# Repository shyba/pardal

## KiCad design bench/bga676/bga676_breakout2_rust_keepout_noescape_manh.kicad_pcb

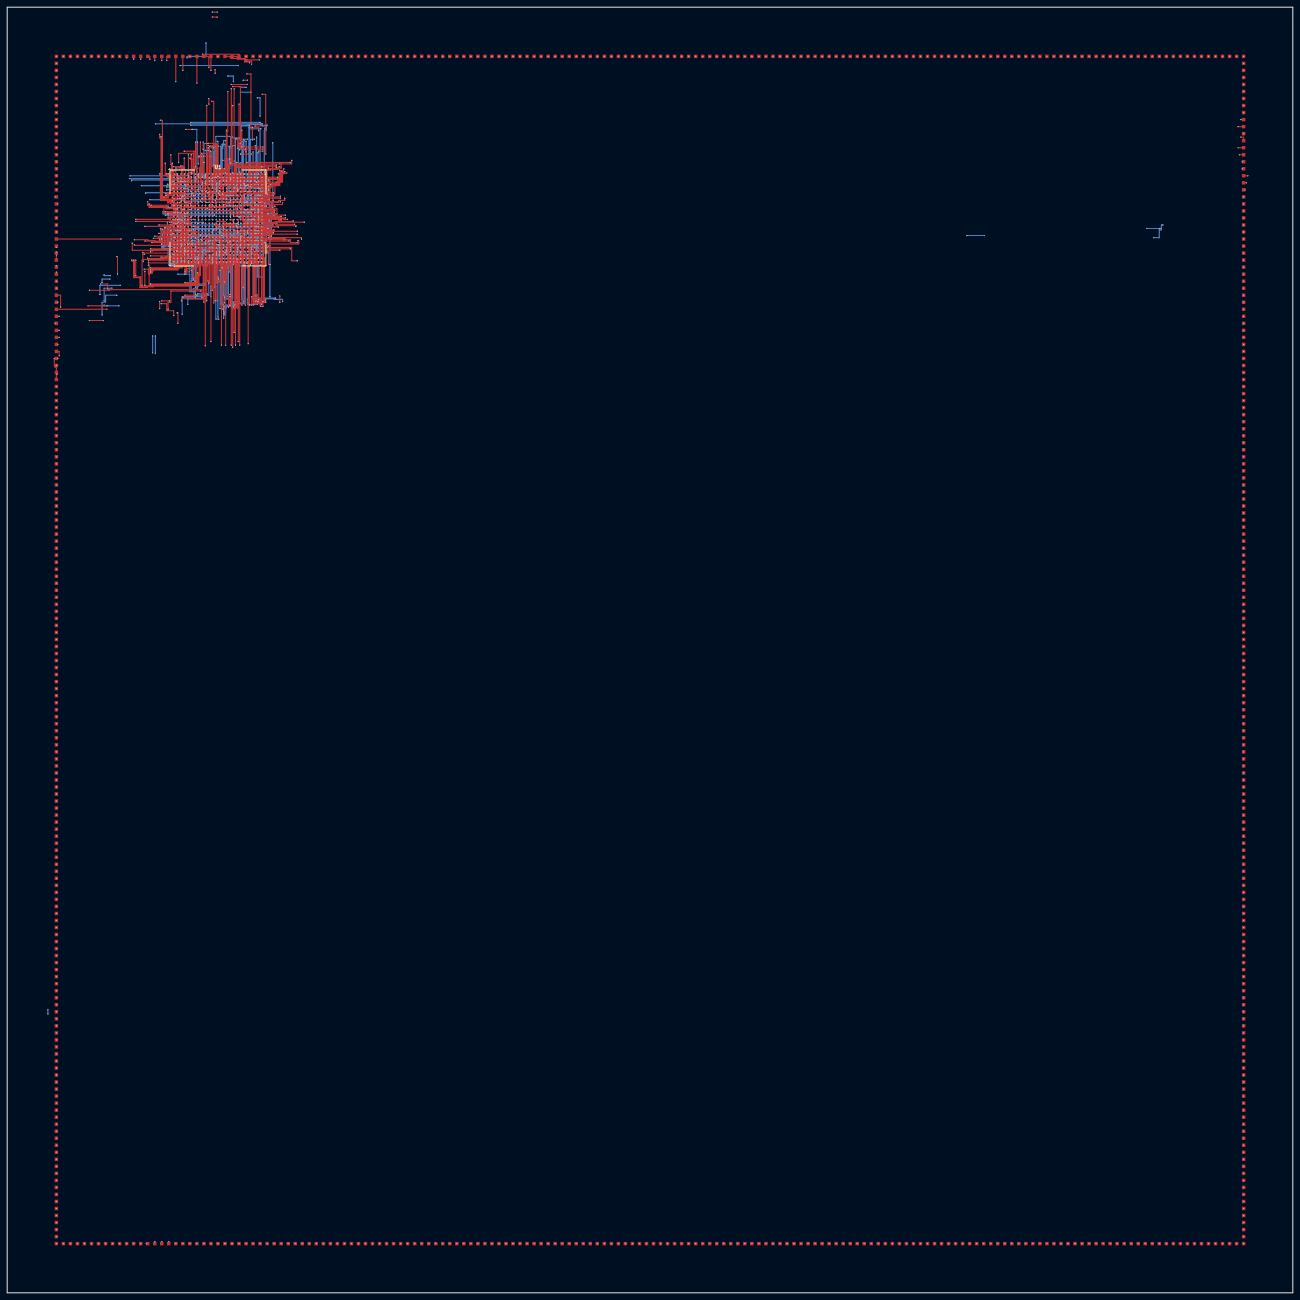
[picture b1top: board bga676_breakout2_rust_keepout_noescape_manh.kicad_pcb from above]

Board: 4 copper layers, 366.0 x 366.0 mm, 677 parts (0 on the bottom side), 676 nets.

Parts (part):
TP1: A1; TestPoint_Pad_1.0x1.0mm
TP2: A2; TestPoint_Pad_1.0x1.0mm
TP3: A3; TestPoint_Pad_1.0x1.0mm
TP4: A4; TestPoint_Pad_1.0x1.0mm
TP5: A5; TestPoint_Pad_1.0x1.0mm
TP6: A6; TestPoint_Pad_1.0x1.0mm
TP7: A7; TestPoint_Pad_1.0x1.0mm
TP8: A8; TestPoint_Pad_1.0x1.0mm
TP9: A9; TestPoint_Pad_1.0x1.0mm
TP10: A10; TestPoint_Pad_1.0x1.0mm
TP11: A11; TestPoint_Pad_1.0x1.0mm
TP12: A12; TestPoint_Pad_1.0x1.0mm
TP13: A13; TestPoint_Pad_1.0x1.0mm
TP14: A14; TestPoint_Pad_1.0x1.0mm
TP15: A15; TestPoint_Pad_1.0x1.0mm
TP16: A16; TestPoint_Pad_1.0x1.0mm
TP17: A17; TestPoint_Pad_1.0x1.0mm
TP18: A18; TestPoint_Pad_1.0x1.0mm
TP19: A19; TestPoint_Pad_1.0x1.0mm
TP20: A20; TestPoint_Pad_1.0x1.0mm
TP21: A21; TestPoint_Pad_1.0x1.0mm
TP22: A22; TestPoint_Pad_1.0x1.0mm
TP23: A23; TestPoint_Pad_1.0x1.0mm
TP24: A24; TestPoint_Pad_1.0x1.0mm
TP25: A25; TestPoint_Pad_1.0x1.0mm
TP26: A26; TestPoint_Pad_1.0x1.0mm
TP27: B1; TestPoint_Pad_1.0x1.0mm
TP28: B2; TestPoint_Pad_1.0x1.0mm
TP29: B3; TestPoint_Pad_1.0x1.0mm
TP30: B4; TestPoint_Pad_1.0x1.0mm
TP31: B5; TestPoint_Pad_1.0x1.0mm
TP32: B6; TestPoint_Pad_1.0x1.0mm
TP33: B7; TestPoint_Pad_1.0x1.0mm
TP34: B8; TestPoint_Pad_1.0x1.0mm
TP35: B9; TestPoint_Pad_1.0x1.0mm
TP36: B10; TestPoint_Pad_1.0x1.0mm
TP37: B11; TestPoint_Pad_1.0x1.0mm
TP38: B12; TestPoint_Pad_1.0x1.0mm
TP39: B13; TestPoint_Pad_1.0x1.0mm
TP40: B14; TestPoint_Pad_1.0x1.0mm
TP41: B15; TestPoint_Pad_1.0x1.0mm
TP42: B16; TestPoint_Pad_1.0x1.0mm
TP43: B17; TestPoint_Pad_1.0x1.0mm
TP44: B18; TestPoint_Pad_1.0x1.0mm
TP45: B19; TestPoint_Pad_1.0x1.0mm
TP46: B20; TestPoint_Pad_1.0x1.0mm
TP47: B21; TestPoint_Pad_1.0x1.0mm
TP48: B22; TestPoint_Pad_1.0x1.0mm
TP49: B23; TestPoint_Pad_1.0x1.0mm
TP50: B24; TestPoint_Pad_1.0x1.0mm
TP51: B25; TestPoint_Pad_1.0x1.0mm
TP52: B26; TestPoint_Pad_1.0x1.0mm
TP53: C1; TestPoint_Pad_1.0x1.0mm
TP54: C2; TestPoint_Pad_1.0x1.0mm
TP55: C3; TestPoint_Pad_1.0x1.0mm
TP56: C4; TestPoint_Pad_1.0x1.0mm
TP57: C5; TestPoint_Pad_1.0x1.0mm
TP58: C6; TestPoint_Pad_1.0x1.0mm
TP59: C7; TestPoint_Pad_1.0x1.0mm
TP60: C8; TestPoint_Pad_1.0x1.0mm
TP61: C9; TestPoint_Pad_1.0x1.0mm
TP62: C10; TestPoint_Pad_1.0x1.0mm
TP63: C11; TestPoint_Pad_1.0x1.0mm
TP64: C12; TestPoint_Pad_1.0x1.0mm
TP65: C13; TestPoint_Pad_1.0x1.0mm
TP66: C14; TestPoint_Pad_1.0x1.0mm
TP67: C15; TestPoint_Pad_1.0x1.0mm
TP68: C16; TestPoint_Pad_1.0x1.0mm
TP69: C17; TestPoint_Pad_1.0x1.0mm
TP70: C18; TestPoint_Pad_1.0x1.0mm
TP71: C19; TestPoint_Pad_1.0x1.0mm
TP72: C20; TestPoint_Pad_1.0x1.0mm
TP73: C21; TestPoint_Pad_1.0x1.0mm
TP74: C22; TestPoint_Pad_1.0x1.0mm
TP75: C23; TestPoint_Pad_1.0x1.0mm
TP76: C24; TestPoint_Pad_1.0x1.0mm
TP77: C25; TestPoint_Pad_1.0x1.0mm
TP78: C26; TestPoint_Pad_1.0x1.0mm
TP79: D1; TestPoint_Pad_1.0x1.0mm
TP80: D2; TestPoint_Pad_1.0x1.0mm
TP81: D3; TestPoint_Pad_1.0x1.0mm
TP82: D4; TestPoint_Pad_1.0x1.0mm
TP83: D5; TestPoint_Pad_1.0x1.0mm
TP84: D6; TestPoint_Pad_1.0x1.0mm
TP85: D7; TestPoint_Pad_1.0x1.0mm
TP86: D8; TestPoint_Pad_1.0x1.0mm
TP87: D9; TestPoint_Pad_1.0x1.0mm
TP88: D10; TestPoint_Pad_1.0x1.0mm
TP89: D11; TestPoint_Pad_1.0x1.0mm
TP90: D12; TestPoint_Pad_1.0x1.0mm
TP91: D13; TestPoint_Pad_1.0x1.0mm
TP92: D14; TestPoint_Pad_1.0x1.0mm
TP93: D15; TestPoint_Pad_1.0x1.0mm
TP94: D16; TestPoint_Pad_1.0x1.0mm
TP95: D17; TestPoint_Pad_1.0x1.0mm
TP96: D18; TestPoint_Pad_1.0x1.0mm
TP97: D19; TestPoint_Pad_1.0x1.0mm
TP98: D20; TestPoint_Pad_1.0x1.0mm
TP99: D21; TestPoint_Pad_1.0x1.0mm
TP100: D22; TestPoint_Pad_1.0x1.0mm
TP101: D23; TestPoint_Pad_1.0x1.0mm
TP102: D24; TestPoint_Pad_1.0x1.0mm
TP103: D25; TestPoint_Pad_1.0x1.0mm
TP104: D26; TestPoint_Pad_1.0x1.0mm
TP105: E1; TestPoint_Pad_1.0x1.0mm
TP106: E2; TestPoint_Pad_1.0x1.0mm
TP107: E3; TestPoint_Pad_1.0x1.0mm
TP108: E4; TestPoint_Pad_1.0x1.0mm
TP109: E5; TestPoint_Pad_1.0x1.0mm
TP110: E6; TestPoint_Pad_1.0x1.0mm
TP111: E7; TestPoint_Pad_1.0x1.0mm
TP112: E8; TestPoint_Pad_1.0x1.0mm
TP113: E9; TestPoint_Pad_1.0x1.0mm
TP114: E10; TestPoint_Pad_1.0x1.0mm
TP115: E11; TestPoint_Pad_1.0x1.0mm
TP116: E12; TestPoint_Pad_1.0x1.0mm
TP117: E13; TestPoint_Pad_1.0x1.0mm
TP118: E14; TestPoint_Pad_1.0x1.0mm
TP119: E15; TestPoint_Pad_1.0x1.0mm
TP120: E16; TestPoint_Pad_1.0x1.0mm
TP121: E17; TestPoint_Pad_1.0x1.0mm
TP122: E18; TestPoint_Pad_1.0x1.0mm
TP123: E19; TestPoint_Pad_1.0x1.0mm
TP124: E20; TestPoint_Pad_1.0x1.0mm
TP125: E21; TestPoint_Pad_1.0x1.0mm
TP126: E22; TestPoint_Pad_1.0x1.0mm
TP127: E23; TestPoint_Pad_1.0x1.0mm
TP128: E24; TestPoint_Pad_1.0x1.0mm
TP129: E25; TestPoint_Pad_1.0x1.0mm
TP130: E26; TestPoint_Pad_1.0x1.0mm
TP131: F1; TestPoint_Pad_1.0x1.0mm
TP132: F2; TestPoint_Pad_1.0x1.0mm
TP133: F3; TestPoint_Pad_1.0x1.0mm
TP134: F4; TestPoint_Pad_1.0x1.0mm
TP135: F5; TestPoint_Pad_1.0x1.0mm
TP136: F6; TestPoint_Pad_1.0x1.0mm
TP137: F7; TestPoint_Pad_1.0x1.0mm
TP138: F8; TestPoint_Pad_1.0x1.0mm
TP139: F9; TestPoint_Pad_1.0x1.0mm
TP140: F10; TestPoint_Pad_1.0x1.0mm
TP141: F11; TestPoint_Pad_1.0x1.0mm
TP142: F12; TestPoint_Pad_1.0x1.0mm
TP143: F13; TestPoint_Pad_1.0x1.0mm
TP144: F14; TestPoint_Pad_1.0x1.0mm
TP145: F15; TestPoint_Pad_1.0x1.0mm
TP146: F16; TestPoint_Pad_1.0x1.0mm
TP147: F17; TestPoint_Pad_1.0x1.0mm
TP148: F18; TestPoint_Pad_1.0x1.0mm
TP149: F19; TestPoint_Pad_1.0x1.0mm
TP150: F20; TestPoint_Pad_1.0x1.0mm
TP151: F21; TestPoint_Pad_1.0x1.0mm
TP152: F22; TestPoint_Pad_1.0x1.0mm
TP153: F23; TestPoint_Pad_1.0x1.0mm
TP154: F24; TestPoint_Pad_1.0x1.0mm
TP155: F25; TestPoint_Pad_1.0x1.0mm
TP156: F26; TestPoint_Pad_1.0x1.0mm
TP157: G1; TestPoint_Pad_1.0x1.0mm
TP158: G2; TestPoint_Pad_1.0x1.0mm
TP159: G3; TestPoint_Pad_1.0x1.0mm
TP160: G4; TestPoint_Pad_1.0x1.0mm
TP161: G5; TestPoint_Pad_1.0x1.0mm
TP162: G6; TestPoint_Pad_1.0x1.0mm
TP163: G7; TestPoint_Pad_1.0x1.0mm
TP164: G8; TestPoint_Pad_1.0x1.0mm
TP165: G9; TestPoint_Pad_1.0x1.0mm
TP166: G10; TestPoint_Pad_1.0x1.0mm
TP167: G11; TestPoint_Pad_1.0x1.0mm
TP168: G12; TestPoint_Pad_1.0x1.0mm
TP169: G13; TestPoint_Pad_1.0x1.0mm
TP170: G14; TestPoint_Pad_1.0x1.0mm
TP171: G15; TestPoint_Pad_1.0x1.0mm
TP172: G16; TestPoint_Pad_1.0x1.0mm
TP173: G17; TestPoint_Pad_1.0x1.0mm
TP174: G18; TestPoint_Pad_1.0x1.0mm
TP175: G19; TestPoint_Pad_1.0x1.0mm
TP176: G20; TestPoint_Pad_1.0x1.0mm
TP177: G21; TestPoint_Pad_1.0x1.0mm
TP178: G22; TestPoint_Pad_1.0x1.0mm
TP179: G23; TestPoint_Pad_1.0x1.0mm
TP180: G24; TestPoint_Pad_1.0x1.0mm
TP181: G25; TestPoint_Pad_1.0x1.0mm
TP182: G26; TestPoint_Pad_1.0x1.0mm
TP183: H1; TestPoint_Pad_1.0x1.0mm
TP184: H2; TestPoint_Pad_1.0x1.0mm
TP185: H3; TestPoint_Pad_1.0x1.0mm
TP186: H4; TestPoint_Pad_1.0x1.0mm
TP187: H5; TestPoint_Pad_1.0x1.0mm
TP188: H6; TestPoint_Pad_1.0x1.0mm
TP189: H7; TestPoint_Pad_1.0x1.0mm
TP190: H8; TestPoint_Pad_1.0x1.0mm
TP191: H9; TestPoint_Pad_1.0x1.0mm
TP192: H10; TestPoint_Pad_1.0x1.0mm
TP193: H11; TestPoint_Pad_1.0x1.0mm
TP194: H12; TestPoint_Pad_1.0x1.0mm
TP195: H13; TestPoint_Pad_1.0x1.0mm
TP196: H14; TestPoint_Pad_1.0x1.0mm
TP197: H15; TestPoint_Pad_1.0x1.0mm
TP198: H16; TestPoint_Pad_1.0x1.0mm
TP199: H17; TestPoint_Pad_1.0x1.0mm
TP200: H18; TestPoint_Pad_1.0x1.0mm
TP201: H19; TestPoint_Pad_1.0x1.0mm
TP202: H20; TestPoint_Pad_1.0x1.0mm
TP203: H21; TestPoint_Pad_1.0x1.0mm
TP204: H22; TestPoint_Pad_1.0x1.0mm
TP205: H23; TestPoint_Pad_1.0x1.0mm
TP206: H24; TestPoint_Pad_1.0x1.0mm
TP207: H25; TestPoint_Pad_1.0x1.0mm
TP208: H26; TestPoint_Pad_1.0x1.0mm
TP209: J1; TestPoint_Pad_1.0x1.0mm
TP210: J2; TestPoint_Pad_1.0x1.0mm
TP211: J3; TestPoint_Pad_1.0x1.0mm
TP212: J4; TestPoint_Pad_1.0x1.0mm
TP213: J5; TestPoint_Pad_1.0x1.0mm
TP214: J6; TestPoint_Pad_1.0x1.0mm
TP215: J7; TestPoint_Pad_1.0x1.0mm
TP216: J8; TestPoint_Pad_1.0x1.0mm
TP217: J9; TestPoint_Pad_1.0x1.0mm
TP218: J10; TestPoint_Pad_1.0x1.0mm
TP219: J11; TestPoint_Pad_1.0x1.0mm
TP220: J12; TestPoint_Pad_1.0x1.0mm
TP221: J13; TestPoint_Pad_1.0x1.0mm
TP222: J14; TestPoint_Pad_1.0x1.0mm
TP223: J15; TestPoint_Pad_1.0x1.0mm
TP224: J16; TestPoint_Pad_1.0x1.0mm
TP225: J17; TestPoint_Pad_1.0x1.0mm
TP226: J18; TestPoint_Pad_1.0x1.0mm
TP227: J19; TestPoint_Pad_1.0x1.0mm
TP228: J20; TestPoint_Pad_1.0x1.0mm
TP229: J21; TestPoint_Pad_1.0x1.0mm
TP230: J22; TestPoint_Pad_1.0x1.0mm
TP231: J23; TestPoint_Pad_1.0x1.0mm
TP232: J24; TestPoint_Pad_1.0x1.0mm
TP233: J25; TestPoint_Pad_1.0x1.0mm
TP234: J26; TestPoint_Pad_1.0x1.0mm
TP235: K1; TestPoint_Pad_1.0x1.0mm
TP236: K2; TestPoint_Pad_1.0x1.0mm
TP237: K3; TestPoint_Pad_1.0x1.0mm
TP238: K4; TestPoint_Pad_1.0x1.0mm
TP239: K5; TestPoint_Pad_1.0x1.0mm
TP240: K6; TestPoint_Pad_1.0x1.0mm
TP241: K7; TestPoint_Pad_1.0x1.0mm
TP242: K8; TestPoint_Pad_1.0x1.0mm
TP243: K9; TestPoint_Pad_1.0x1.0mm
TP244: K10; TestPoint_Pad_1.0x1.0mm
TP245: K11; TestPoint_Pad_1.0x1.0mm
TP246: K12; TestPoint_Pad_1.0x1.0mm
TP247: K13; TestPoint_Pad_1.0x1.0mm
TP248: K14; TestPoint_Pad_1.0x1.0mm
TP249: K15; TestPoint_Pad_1.0x1.0mm
TP250: K16; TestPoint_Pad_1.0x1.0mm
TP251: K17; TestPoint_Pad_1.0x1.0mm
TP252: K18; TestPoint_Pad_1.0x1.0mm
TP253: K19; TestPoint_Pad_1.0x1.0mm
TP254: K20; TestPoint_Pad_1.0x1.0mm
TP255: K21; TestPoint_Pad_1.0x1.0mm
TP256: K22; TestPoint_Pad_1.0x1.0mm
TP257: K23; TestPoint_Pad_1.0x1.0mm
TP258: K24; TestPoint_Pad_1.0x1.0mm
TP259: K25; TestPoint_Pad_1.0x1.0mm
TP260: K26; TestPoint_Pad_1.0x1.0mm
TP261: L1; TestPoint_Pad_1.0x1.0mm
TP262: L2; TestPoint_Pad_1.0x1.0mm
TP263: L3; TestPoint_Pad_1.0x1.0mm
TP264: L4; TestPoint_Pad_1.0x1.0mm
TP265: L5; TestPoint_Pad_1.0x1.0mm
TP266: L6; TestPoint_Pad_1.0x1.0mm
TP267: L7; TestPoint_Pad_1.0x1.0mm
TP268: L8; TestPoint_Pad_1.0x1.0mm
TP269: L9; TestPoint_Pad_1.0x1.0mm
TP270: L10; TestPoint_Pad_1.0x1.0mm
TP271: L11; TestPoint_Pad_1.0x1.0mm
TP272: L12; TestPoint_Pad_1.0x1.0mm
TP273: L13; TestPoint_Pad_1.0x1.0mm
TP274: L14; TestPoint_Pad_1.0x1.0mm
TP275: L15; TestPoint_Pad_1.0x1.0mm
TP276: L16; TestPoint_Pad_1.0x1.0mm
TP277: L17; TestPoint_Pad_1.0x1.0mm
TP278: L18; TestPoint_Pad_1.0x1.0mm
TP279: L19; TestPoint_Pad_1.0x1.0mm
TP280: L20; TestPoint_Pad_1.0x1.0mm
TP281: L21; TestPoint_Pad_1.0x1.0mm
TP282: L22; TestPoint_Pad_1.0x1.0mm
TP283: L23; TestPoint_Pad_1.0x1.0mm
TP284: L24; TestPoint_Pad_1.0x1.0mm
TP285: L25; TestPoint_Pad_1.0x1.0mm
TP286: L26; TestPoint_Pad_1.0x1.0mm
TP287: M1; TestPoint_Pad_1.0x1.0mm
TP288: M2; TestPoint_Pad_1.0x1.0mm
TP289: M3; TestPoint_Pad_1.0x1.0mm
TP290: M4; TestPoint_Pad_1.0x1.0mm
TP291: M5; TestPoint_Pad_1.0x1.0mm
TP292: M6; TestPoint_Pad_1.0x1.0mm
TP293: M7; TestPoint_Pad_1.0x1.0mm
TP294: M8; TestPoint_Pad_1.0x1.0mm
TP295: M9; TestPoint_Pad_1.0x1.0mm
TP296: M10; TestPoint_Pad_1.0x1.0mm
TP297: M11; TestPoint_Pad_1.0x1.0mm
TP298: M12; TestPoint_Pad_1.0x1.0mm
TP299: M13; TestPoint_Pad_1.0x1.0mm
TP300: M14; TestPoint_Pad_1.0x1.0mm
TP301: M15; TestPoint_Pad_1.0x1.0mm
TP302: M16; TestPoint_Pad_1.0x1.0mm
TP303: M17; TestPoint_Pad_1.0x1.0mm
TP304: M18; TestPoint_Pad_1.0x1.0mm
TP305: M19; TestPoint_Pad_1.0x1.0mm
TP306: M20; TestPoint_Pad_1.0x1.0mm
TP307: M21; TestPoint_Pad_1.0x1.0mm
TP308: M22; TestPoint_Pad_1.0x1.0mm
TP309: M23; TestPoint_Pad_1.0x1.0mm
TP310: M24; TestPoint_Pad_1.0x1.0mm
TP311: M25; TestPoint_Pad_1.0x1.0mm
TP312: M26; TestPoint_Pad_1.0x1.0mm
TP313: N1; TestPoint_Pad_1.0x1.0mm
TP314: N2; TestPoint_Pad_1.0x1.0mm
TP315: N3; TestPoint_Pad_1.0x1.0mm
TP316: N4; TestPoint_Pad_1.0x1.0mm
TP317: N5; TestPoint_Pad_1.0x1.0mm
TP318: N6; TestPoint_Pad_1.0x1.0mm
TP319: N7; TestPoint_Pad_1.0x1.0mm
TP320: N8; TestPoint_Pad_1.0x1.0mm
TP321: N9; TestPoint_Pad_1.0x1.0mm
TP322: N10; TestPoint_Pad_1.0x1.0mm
TP323: N11; TestPoint_Pad_1.0x1.0mm
TP324: N12; TestPoint_Pad_1.0x1.0mm
TP325: N13; TestPoint_Pad_1.0x1.0mm
TP326: N14; TestPoint_Pad_1.0x1.0mm
TP327: N15; TestPoint_Pad_1.0x1.0mm
TP328: N16; TestPoint_Pad_1.0x1.0mm
TP329: N17; TestPoint_Pad_1.0x1.0mm
TP330: N18; TestPoint_Pad_1.0x1.0mm
TP331: N19; TestPoint_Pad_1.0x1.0mm
TP332: N20; TestPoint_Pad_1.0x1.0mm
TP333: N21; TestPoint_Pad_1.0x1.0mm
TP334: N22; TestPoint_Pad_1.0x1.0mm
TP335: N23; TestPoint_Pad_1.0x1.0mm
TP336: N24; TestPoint_Pad_1.0x1.0mm
TP337: N25; TestPoint_Pad_1.0x1.0mm
TP338: N26; TestPoint_Pad_1.0x1.0mm
TP339: P1; TestPoint_Pad_1.0x1.0mm
TP340: P2; TestPoint_Pad_1.0x1.0mm
TP341: P3; TestPoint_Pad_1.0x1.0mm
TP342: P4; TestPoint_Pad_1.0x1.0mm
TP343: P5; TestPoint_Pad_1.0x1.0mm
TP344: P6; TestPoint_Pad_1.0x1.0mm
TP345: P7; TestPoint_Pad_1.0x1.0mm
TP346: P8; TestPoint_Pad_1.0x1.0mm
TP347: P9; TestPoint_Pad_1.0x1.0mm
TP348: P10; TestPoint_Pad_1.0x1.0mm
TP349: P11; TestPoint_Pad_1.0x1.0mm
TP350: P12; TestPoint_Pad_1.0x1.0mm
TP351: P13; TestPoint_Pad_1.0x1.0mm
TP352: P14; TestPoint_Pad_1.0x1.0mm
TP353: P15; TestPoint_Pad_1.0x1.0mm
TP354: P16; TestPoint_Pad_1.0x1.0mm
TP355: P17; TestPoint_Pad_1.0x1.0mm
TP356: P18; TestPoint_Pad_1.0x1.0mm
TP357: P19; TestPoint_Pad_1.0x1.0mm
TP358: P20; TestPoint_Pad_1.0x1.0mm
TP359: P21; TestPoint_Pad_1.0x1.0mm
TP360: P22; TestPoint_Pad_1.0x1.0mm
TP361: P23; TestPoint_Pad_1.0x1.0mm
TP362: P24; TestPoint_Pad_1.0x1.0mm
TP363: P25; TestPoint_Pad_1.0x1.0mm
TP364: P26; TestPoint_Pad_1.0x1.0mm
TP365: R1; TestPoint_Pad_1.0x1.0mm
TP366: R2; TestPoint_Pad_1.0x1.0mm
TP367: R3; TestPoint_Pad_1.0x1.0mm
TP368: R4; TestPoint_Pad_1.0x1.0mm
TP369: R5; TestPoint_Pad_1.0x1.0mm
TP370: R6; TestPoint_Pad_1.0x1.0mm
TP371: R7; TestPoint_Pad_1.0x1.0mm
TP372: R8; TestPoint_Pad_1.0x1.0mm
TP373: R9; TestPoint_Pad_1.0x1.0mm
TP374: R10; TestPoint_Pad_1.0x1.0mm
TP375: R11; TestPoint_Pad_1.0x1.0mm
TP376: R12; TestPoint_Pad_1.0x1.0mm
TP377: R13; TestPoint_Pad_1.0x1.0mm
TP378: R14; TestPoint_Pad_1.0x1.0mm
TP379: R15; TestPoint_Pad_1.0x1.0mm
TP380: R16; TestPoint_Pad_1.0x1.0mm
TP381: R17; TestPoint_Pad_1.0x1.0mm
TP382: R18; TestPoint_Pad_1.0x1.0mm
TP383: R19; TestPoint_Pad_1.0x1.0mm
TP384: R20; TestPoint_Pad_1.0x1.0mm
TP385: R21; TestPoint_Pad_1.0x1.0mm
TP386: R22; TestPoint_Pad_1.0x1.0mm
TP387: R23; TestPoint_Pad_1.0x1.0mm
TP388: R24; TestPoint_Pad_1.0x1.0mm
TP389: R25; TestPoint_Pad_1.0x1.0mm
TP390: R26; TestPoint_Pad_1.0x1.0mm
TP391: T1; TestPoint_Pad_1.0x1.0mm
TP392: T2; TestPoint_Pad_1.0x1.0mm
TP393: T3; TestPoint_Pad_1.0x1.0mm
TP394: T4; TestPoint_Pad_1.0x1.0mm
TP395: T5; TestPoint_Pad_1.0x1.0mm
TP396: T6; TestPoint_Pad_1.0x1.0mm
TP397: T7; TestPoint_Pad_1.0x1.0mm
TP398: T8; TestPoint_Pad_1.0x1.0mm
TP399: T9; TestPoint_Pad_1.0x1.0mm
TP400: T10; TestPoint_Pad_1.0x1.0mm
TP401: T11; TestPoint_Pad_1.0x1.0mm
TP402: T12; TestPoint_Pad_1.0x1.0mm
TP403: T13; TestPoint_Pad_1.0x1.0mm
TP404: T14; TestPoint_Pad_1.0x1.0mm
TP405: T15; TestPoint_Pad_1.0x1.0mm
TP406: T16; TestPoint_Pad_1.0x1.0mm
TP407: T17; TestPoint_Pad_1.0x1.0mm
TP408: T18; TestPoint_Pad_1.0x1.0mm
TP409: T19; TestPoint_Pad_1.0x1.0mm
TP410: T20; TestPoint_Pad_1.0x1.0mm
TP411: T21; TestPoint_Pad_1.0x1.0mm
TP412: T22; TestPoint_Pad_1.0x1.0mm
TP413: T23; TestPoint_Pad_1.0x1.0mm
TP414: T24; TestPoint_Pad_1.0x1.0mm
TP415: T25; TestPoint_Pad_1.0x1.0mm
TP416: T26; TestPoint_Pad_1.0x1.0mm
TP417: U1; TestPoint_Pad_1.0x1.0mm
TP418: U2; TestPoint_Pad_1.0x1.0mm
TP419: U3; TestPoint_Pad_1.0x1.0mm
TP420: U4; TestPoint_Pad_1.0x1.0mm
TP421: U5; TestPoint_Pad_1.0x1.0mm
TP422: U6; TestPoint_Pad_1.0x1.0mm
TP423: U7; TestPoint_Pad_1.0x1.0mm
TP424: U8; TestPoint_Pad_1.0x1.0mm
TP425: U9; TestPoint_Pad_1.0x1.0mm
TP426: U10; TestPoint_Pad_1.0x1.0mm
TP427: U11; TestPoint_Pad_1.0x1.0mm
TP428: U12; TestPoint_Pad_1.0x1.0mm
TP429: U13; TestPoint_Pad_1.0x1.0mm
TP430: U14; TestPoint_Pad_1.0x1.0mm
TP431: U15; TestPoint_Pad_1.0x1.0mm
TP432: U16; TestPoint_Pad_1.0x1.0mm
TP433: U17; TestPoint_Pad_1.0x1.0mm
TP434: U18; TestPoint_Pad_1.0x1.0mm
TP435: U19; TestPoint_Pad_1.0x1.0mm
TP436: U20; TestPoint_Pad_1.0x1.0mm
TP437: U21; TestPoint_Pad_1.0x1.0mm
TP438: U22; TestPoint_Pad_1.0x1.0mm
TP439: U23; TestPoint_Pad_1.0x1.0mm
TP440: U24; TestPoint_Pad_1.0x1.0mm
TP441: U25; TestPoint_Pad_1.0x1.0mm
TP442: U26; TestPoint_Pad_1.0x1.0mm
TP443: V1; TestPoint_Pad_1.0x1.0mm
TP444: V2; TestPoint_Pad_1.0x1.0mm
TP445: V3; TestPoint_Pad_1.0x1.0mm
TP446: V4; TestPoint_Pad_1.0x1.0mm
TP447: V5; TestPoint_Pad_1.0x1.0mm
TP448: V6; TestPoint_Pad_1.0x1.0mm
TP449: V7; TestPoint_Pad_1.0x1.0mm
TP450: V8; TestPoint_Pad_1.0x1.0mm
TP451: V9; TestPoint_Pad_1.0x1.0mm
TP452: V10; TestPoint_Pad_1.0x1.0mm
TP453: V11; TestPoint_Pad_1.0x1.0mm
TP454: V12; TestPoint_Pad_1.0x1.0mm
TP455: V13; TestPoint_Pad_1.0x1.0mm
TP456: V14; TestPoint_Pad_1.0x1.0mm
TP457: V15; TestPoint_Pad_1.0x1.0mm
TP458: V16; TestPoint_Pad_1.0x1.0mm
TP459: V17; TestPoint_Pad_1.0x1.0mm
TP460: V18; TestPoint_Pad_1.0x1.0mm
TP461: V19; TestPoint_Pad_1.0x1.0mm
TP462: V20; TestPoint_Pad_1.0x1.0mm
TP463: V21; TestPoint_Pad_1.0x1.0mm
TP464: V22; TestPoint_Pad_1.0x1.0mm
TP465: V23; TestPoint_Pad_1.0x1.0mm
TP466: V24; TestPoint_Pad_1.0x1.0mm
TP467: V25; TestPoint_Pad_1.0x1.0mm
TP468: V26; TestPoint_Pad_1.0x1.0mm
TP469: W1; TestPoint_Pad_1.0x1.0mm
TP470: W2; TestPoint_Pad_1.0x1.0mm
TP471: W3; TestPoint_Pad_1.0x1.0mm
TP472: W4; TestPoint_Pad_1.0x1.0mm
TP473: W5; TestPoint_Pad_1.0x1.0mm
TP474: W6; TestPoint_Pad_1.0x1.0mm
TP475: W7; TestPoint_Pad_1.0x1.0mm
TP476: W8; TestPoint_Pad_1.0x1.0mm
TP477: W9; TestPoint_Pad_1.0x1.0mm
TP478: W10; TestPoint_Pad_1.0x1.0mm
TP479: W11; TestPoint_Pad_1.0x1.0mm
TP480: W12; TestPoint_Pad_1.0x1.0mm
TP481: W13; TestPoint_Pad_1.0x1.0mm
TP482: W14; TestPoint_Pad_1.0x1.0mm
TP483: W15; TestPoint_Pad_1.0x1.0mm
TP484: W16; TestPoint_Pad_1.0x1.0mm
TP485: W17; TestPoint_Pad_1.0x1.0mm
TP486: W18; TestPoint_Pad_1.0x1.0mm
TP487: W19; TestPoint_Pad_1.0x1.0mm
TP488: W20; TestPoint_Pad_1.0x1.0mm
TP489: W21; TestPoint_Pad_1.0x1.0mm
TP490: W22; TestPoint_Pad_1.0x1.0mm
TP491: W23; TestPoint_Pad_1.0x1.0mm
TP492: W24; TestPoint_Pad_1.0x1.0mm
TP493: W25; TestPoint_Pad_1.0x1.0mm
TP494: W26; TestPoint_Pad_1.0x1.0mm
TP495: Y1; TestPoint_Pad_1.0x1.0mm
TP496: Y2; TestPoint_Pad_1.0x1.0mm
TP497: Y3; TestPoint_Pad_1.0x1.0mm
TP498: Y4; TestPoint_Pad_1.0x1.0mm
TP499: Y5; TestPoint_Pad_1.0x1.0mm
TP500: Y6; TestPoint_Pad_1.0x1.0mm
TP501: Y7; TestPoint_Pad_1.0x1.0mm
TP502: Y8; TestPoint_Pad_1.0x1.0mm
TP503: Y9; TestPoint_Pad_1.0x1.0mm
TP504: Y10; TestPoint_Pad_1.0x1.0mm
TP505: Y11; TestPoint_Pad_1.0x1.0mm
TP506: Y12; TestPoint_Pad_1.0x1.0mm
TP507: Y13; TestPoint_Pad_1.0x1.0mm
TP508: Y14; TestPoint_Pad_1.0x1.0mm
TP509: Y15; TestPoint_Pad_1.0x1.0mm
TP510: Y16; TestPoint_Pad_1.0x1.0mm
TP511: Y17; TestPoint_Pad_1.0x1.0mm
TP512: Y18; TestPoint_Pad_1.0x1.0mm
TP513: Y19; TestPoint_Pad_1.0x1.0mm
TP514: Y20; TestPoint_Pad_1.0x1.0mm
TP515: Y21; TestPoint_Pad_1.0x1.0mm
TP516: Y22; TestPoint_Pad_1.0x1.0mm
TP517: Y23; TestPoint_Pad_1.0x1.0mm
TP518: Y24; TestPoint_Pad_1.0x1.0mm
TP519: Y25; TestPoint_Pad_1.0x1.0mm
TP520: Y26; TestPoint_Pad_1.0x1.0mm
TP521: AA1; TestPoint_Pad_1.0x1.0mm
TP522: AA2; TestPoint_Pad_1.0x1.0mm
TP523: AA3; TestPoint_Pad_1.0x1.0mm
TP524: AA4; TestPoint_Pad_1.0x1.0mm
TP525: AA5; TestPoint_Pad_1.0x1.0mm
TP526: AA6; TestPoint_Pad_1.0x1.0mm
TP527: AA7; TestPoint_Pad_1.0x1.0mm
TP528: AA8; TestPoint_Pad_1.0x1.0mm
TP529: AA9; TestPoint_Pad_1.0x1.0mm
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
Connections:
U1_A1: TP1.1, U1.A1
U1_A2: TP2.1, U1.A2
U1_A3: TP3.1, U1.A3
U1_A4: TP4.1, U1.A4
U1_A5: TP5.1, U1.A5
U1_A6: TP6.1, U1.A6
U1_A7: TP7.1, U1.A7
U1_A8: TP8.1, U1.A8
U1_A9: TP9.1, U1.A9
U1_A10: TP10.1, U1.A10
U1_A11: TP11.1, U1.A11
U1_A12: TP12.1, U1.A12
U1_A13: TP13.1, U1.A13
U1_A14: TP14.1, U1.A14
U1_A15: TP15.1, U1.A15
U1_A16: TP16.1, U1.A16
U1_A17: TP17.1, U1.A17
U1_A18: TP18.1, U1.A18
U1_A19: TP19.1, U1.A19
U1_A20: TP20.1, U1.A20
U1_A21: TP21.1, U1.A21
U1_A22: TP22.1, U1.A22
U1_A23: TP23.1, U1.A23
U1_A24: TP24.1, U1.A24
U1_A25: TP25.1, U1.A25
U1_A26: TP26.1, U1.A26
U1_AA1: TP521.1, U1.AA1
U1_AA2: TP522.1, U1.AA2
U1_AA3: TP523.1, U1.AA3
U1_AA4: TP524.1, U1.AA4
U1_AA5: TP525.1, U1.AA5
U1_AA6: TP526.1, U1.AA6
U1_AA7: TP527.1, U1.AA7
U1_AA8: TP528.1, U1.AA8
U1_AA9: TP529.1, U1.AA9
U1_AA10: TP530.1, U1.AA10
U1_AA11: TP531.1, U1.AA11
U1_AA12: TP532.1, U1.AA12
U1_AA13: TP533.1, U1.AA13
U1_AA14: TP534.1, U1.AA14
U1_AA15: TP535.1, U1.AA15
U1_AA16: TP536.1, U1.AA16
U1_AA17: TP537.1, U1.AA17
U1_AA18: TP538.1, U1.AA18
U1_AA19: TP539.1, U1.AA19
U1_AA20: TP540.1, U1.AA20
U1_AA21: TP541.1, U1.AA21
U1_AA22: TP542.1, U1.AA22
U1_AA23: TP543.1, U1.AA23
U1_AA24: TP544.1, U1.AA24
U1_AA25: TP545.1, U1.AA25
U1_AA26: TP546.1, U1.AA26
U1_AB1: TP547.1, U1.AB1
U1_AB2: TP548.1, U1.AB2
U1_AB3: TP549.1, U1.AB3
U1_AB4: TP550.1, U1.AB4
U1_AB5: TP551.1, U1.AB5
U1_AB6: TP552.1, U1.AB6
U1_AB7: TP553.1, U1.AB7
U1_AB8: TP554.1, U1.AB8
U1_AB9: TP555.1, U1.AB9
U1_AB10: TP556.1, U1.AB10
U1_AB11: TP557.1, U1.AB11
U1_AB12: TP558.1, U1.AB12
U1_AB13: TP559.1, U1.AB13
U1_AB14: TP560.1, U1.AB14
U1_AB15: TP561.1, U1.AB15
U1_AB16: TP562.1, U1.AB16
U1_AB17: TP563.1, U1.AB17
U1_AB18: TP564.1, U1.AB18
U1_AB19: TP565.1, U1.AB19
U1_AB20: TP566.1, U1.AB20
U1_AB21: TP567.1, U1.AB21
U1_AB22: TP568.1, U1.AB22
U1_AB23: TP569.1, U1.AB23
U1_AB24: TP570.1, U1.AB24
U1_AB25: TP571.1, U1.AB25
U1_AB26: TP572.1, U1.AB26
U1_AC1: TP573.1, U1.AC1
U1_AC2: TP574.1, U1.AC2
U1_AC3: TP575.1, U1.AC3
U1_AC4: TP576.1, U1.AC4
U1_AC5: TP577.1, U1.AC5
U1_AC6: TP578.1, U1.AC6
U1_AC7: TP579.1, U1.AC7
U1_AC8: TP580.1, U1.AC8
U1_AC9: TP581.1, U1.AC9
U1_AC10: TP582.1, U1.AC10
U1_AC11: TP583.1, U1.AC11
U1_AC12: TP584.1, U1.AC12
U1_AC13: TP585.1, U1.AC13
U1_AC14: TP586.1, U1.AC14
U1_AC15: TP587.1, U1.AC15
U1_AC16: TP588.1, U1.AC16
U1_AC17: TP589.1, U1.AC17
U1_AC18: TP590.1, U1.AC18
U1_AC19: TP591.1, U1.AC19
U1_AC20: TP592.1, U1.AC20
U1_AC21: TP593.1, U1.AC21
U1_AC22: TP594.1, U1.AC22
U1_AC23: TP595.1, U1.AC23
U1_AC24: TP596.1, U1.AC24
U1_AC25: TP597.1, U1.AC25
U1_AC26: TP598.1, U1.AC26
U1_AD1: TP599.1, U1.AD1
U1_AD2: TP600.1, U1.AD2
U1_AD3: TP601.1, U1.AD3
U1_AD4: TP602.1, U1.AD4
U1_AD5: TP603.1, U1.AD5
U1_AD6: TP604.1, U1.AD6
U1_AD7: TP605.1, U1.AD7
U1_AD8: TP606.1, U1.AD8
U1_AD9: TP607.1, U1.AD9
U1_AD10: TP608.1, U1.AD10
U1_AD11: TP609.1, U1.AD11
U1_AD12: TP610.1, U1.AD12
U1_AD13: TP611.1, U1.AD13
U1_AD14: TP612.1, U1.AD14
U1_AD15: TP613.1, U1.AD15
U1_AD16: TP614.1, U1.AD16
U1_AD17: TP615.1, U1.AD17
U1_AD18: TP616.1, U1.AD18
U1_AD19: TP617.1, U1.AD19
U1_AD20: TP618.1, U1.AD20
U1_AD21: TP619.1, U1.AD21
U1_AD22: TP620.1, U1.AD22
U1_AD23: TP621.1, U1.AD23
U1_AD24: TP622.1, U1.AD24
U1_AD25: TP623.1, U1.AD25
U1_AD26: TP624.1, U1.AD26
U1_AE1: TP625.1, U1.AE1
U1_AE2: TP626.1, U1.AE2
U1_AE3: TP627.1, U1.AE3
U1_AE4: TP628.1, U1.AE4
U1_AE5: TP629.1, U1.AE5
U1_AE6: TP630.1, U1.AE6
U1_AE7: TP631.1, U1.AE7
U1_AE8: TP632.1, U1.AE8
U1_AE9: TP633.1, U1.AE9
U1_AE10: TP634.1, U1.AE10
U1_AE11: TP635.1, U1.AE11
U1_AE12: TP636.1, U1.AE12
U1_AE13: TP637.1, U1.AE13
U1_AE14: TP638.1, U1.AE14
U1_AE15: TP639.1, U1.AE15
U1_AE16: TP640.1, U1.AE16
U1_AE17: TP641.1, U1.AE17
U1_AE18: TP642.1, U1.AE18
U1_AE19: TP643.1, U1.AE19
U1_AE20: TP644.1, U1.AE20
U1_AE21: TP645.1, U1.AE21
U1_AE22: TP646.1, U1.AE22
U1_AE23: TP647.1, U1.AE23
U1_AE24: TP648.1, U1.AE24
U1_AE25: TP649.1, U1.AE25
U1_AE26: TP650.1, U1.AE26
U1_AF1: TP651.1, U1.AF1
U1_AF2: TP652.1, U1.AF2
U1_AF3: TP653.1, U1.AF3
U1_AF4: TP654.1, U1.AF4
U1_AF5: TP655.1, U1.AF5
U1_AF6: TP656.1, U1.AF6
U1_AF7: TP657.1, U1.AF7
U1_AF8: TP658.1, U1.AF8
U1_AF9: TP659.1, U1.AF9
U1_AF10: TP660.1, U1.AF10
U1_AF11: TP661.1, U1.AF11
U1_AF12: TP662.1, U1.AF12
U1_AF13: TP663.1, U1.AF13
U1_AF14: TP664.1, U1.AF14
U1_AF15: TP665.1, U1.AF15
U1_AF16: TP666.1, U1.AF16
U1_AF17: TP667.1, U1.AF17
U1_AF18: TP668.1, U1.AF18
U1_AF19: TP669.1, U1.AF19
U1_AF20: TP670.1, U1.AF20
U1_AF21: TP671.1, U1.AF21
U1_AF22: TP672.1, U1.AF22
U1_AF23: TP673.1, U1.AF23
U1_AF24: TP674.1, U1.AF24
U1_AF25: TP675.1, U1.AF25
U1_AF26: TP676.1, U1.AF26
U1_B1: TP27.1, U1.B1
U1_B2: TP28.1, U1.B2
U1_B3: TP29.1, U1.B3
U1_B4: TP30.1, U1.B4
U1_B5: TP31.1, U1.B5
U1_B6: TP32.1, U1.B6
U1_B7: TP33.1, U1.B7
U1_B8: TP34.1, U1.B8
U1_B9: TP35.1, U1.B9
U1_B10: TP36.1, U1.B10
U1_B11: TP37.1, U1.B11
U1_B12: TP38.1, U1.B12
U1_B13: TP39.1, U1.B13
U1_B14: TP40.1, U1.B14
U1_B15: TP41.1, U1.B15
U1_B16: TP42.1, U1.B16
U1_B17: TP43.1, U1.B17
U1_B18: TP44.1, U1.B18
U1_B19: TP45.1, U1.B19
U1_B20: TP46.1, U1.B20
U1_B21: TP47.1, U1.B21
U1_B22: TP48.1, U1.B22
U1_B23: TP49.1, U1.B23
U1_B24: TP50.1, U1.B24
U1_B25: TP51.1, U1.B25
U1_B26: TP52.1, U1.B26
U1_C1: TP53.1, U1.C1
U1_C2: TP54.1, U1.C2
U1_C3: TP55.1, U1.C3
U1_C4: TP56.1, U1.C4
U1_C5: TP57.1, U1.C5
U1_C6: TP58.1, U1.C6
U1_C7: TP59.1, U1.C7
U1_C8: TP60.1, U1.C8
U1_C9: TP61.1, U1.C9
U1_C10: TP62.1, U1.C10
U1_C11: TP63.1, U1.C11
U1_C12: TP64.1, U1.C12
U1_C13: TP65.1, U1.C13
U1_C14: TP66.1, U1.C14
U1_C15: TP67.1, U1.C15
U1_C16: TP68.1, U1.C16
U1_C17: TP69.1, U1.C17
U1_C18: TP70.1, U1.C18
U1_C19: TP71.1, U1.C19
U1_C20: TP72.1, U1.C20
U1_C21: TP73.1, U1.C21
U1_C22: TP74.1, U1.C22
U1_C23: TP75.1, U1.C23
U1_C24: TP76.1, U1.C24
U1_C25: TP77.1, U1.C25
U1_C26: TP78.1, U1.C26
U1_D1: TP79.1, U1.D1
U1_D2: TP80.1, U1.D2
U1_D3: TP81.1, U1.D3
U1_D4: TP82.1, U1.D4
U1_D5: TP83.1, U1.D5
U1_D6: TP84.1, U1.D6
U1_D7: TP85.1, U1.D7
U1_D8: TP86.1, U1.D8
U1_D9: TP87.1, U1.D9
U1_D10: TP88.1, U1.D10
U1_D11: TP89.1, U1.D11
U1_D12: TP90.1, U1.D12
U1_D13: TP91.1, U1.D13
U1_D14: TP92.1, U1.D14
U1_D15: TP93.1, U1.D15
U1_D16: TP94.1, U1.D16
U1_D17: TP95.1, U1.D17
U1_D18: TP96.1, U1.D18
U1_D19: TP97.1, U1.D19
U1_D20: TP98.1, U1.D20
U1_D21: TP99.1, U1.D21
U1_D22: TP100.1, U1.D22
U1_D23: TP101.1, U1.D23
U1_D24: TP102.1, U1.D24
U1_D25: TP103.1, U1.D25
U1_D26: TP104.1, U1.D26
U1_E1: TP105.1, U1.E1
U1_E2: TP106.1, U1.E2
U1_E3: TP107.1, U1.E3
U1_E4: TP108.1, U1.E4
U1_E5: TP109.1, U1.E5
U1_E6: TP110.1, U1.E6
U1_E7: TP111.1, U1.E7
U1_E8: TP112.1, U1.E8
U1_E9: TP113.1, U1.E9
U1_E10: TP114.1, U1.E10
U1_E11: TP115.1, U1.E11
U1_E12: TP116.1, U1.E12
U1_E13: TP117.1, U1.E13
U1_E14: TP118.1, U1.E14
U1_E15: TP119.1, U1.E15
U1_E16: TP120.1, U1.E16
U1_E17: TP121.1, U1.E17
U1_E18: TP122.1, U1.E18
U1_E19: TP123.1, U1.E19
U1_E20: TP124.1, U1.E20
U1_E21: TP125.1, U1.E21
U1_E22: TP126.1, U1.E22
U1_E23: TP127.1, U1.E23
U1_E24: TP128.1, U1.E24
U1_E25: TP129.1, U1.E25
U1_E26: TP130.1, U1.E26
U1_F1: TP131.1, U1.F1
U1_F2: TP132.1, U1.F2
U1_F3: TP133.1, U1.F3
U1_F4: TP134.1, U1.F4
U1_F5: TP135.1, U1.F5
U1_F6: TP136.1, U1.F6
U1_F7: TP137.1, U1.F7
U1_F8: TP138.1, U1.F8
U1_F9: TP139.1, U1.F9
U1_F10: TP140.1, U1.F10
U1_F11: TP141.1, U1.F11
U1_F12: TP142.1, U1.F12
U1_F13: TP143.1, U1.F13
U1_F14: TP144.1, U1.F14
U1_F15: TP145.1, U1.F15
U1_F16: TP146.1, U1.F16
U1_F17: TP147.1, U1.F17
U1_F18: TP148.1, U1.F18
U1_F19: TP149.1, U1.F19
U1_F20: TP150.1, U1.F20
U1_F21: TP151.1, U1.F21
U1_F22: TP152.1, U1.F22
U1_F23: TP153.1, U1.F23
U1_F24: TP154.1, U1.F24
U1_F25: TP155.1, U1.F25
U1_F26: TP156.1, U1.F26
U1_G1: TP157.1, U1.G1
U1_G2: TP158.1, U1.G2
U1_G3: TP159.1, U1.G3
U1_G4: TP160.1, U1.G4
U1_G5: TP161.1, U1.G5
U1_G6: TP162.1, U1.G6
U1_G7: TP163.1, U1.G7
U1_G8: TP164.1, U1.G8
U1_G9: TP165.1, U1.G9
U1_G10: TP166.1, U1.G10
U1_G11: TP167.1, U1.G11
U1_G12: TP168.1, U1.G12
U1_G13: TP169.1, U1.G13
U1_G14: TP170.1, U1.G14
U1_G15: TP171.1, U1.G15
U1_G16: TP172.1, U1.G16
U1_G17: TP173.1, U1.G17
U1_G18: TP174.1, U1.G18
U1_G19: TP175.1, U1.G19
U1_G20: TP176.1, U1.G20
U1_G21: TP177.1, U1.G21
U1_G22: TP178.1, U1.G22
U1_G23: TP179.1, U1.G23
U1_G24: TP180.1, U1.G24
U1_G25: TP181.1, U1.G25
U1_G26: TP182.1, U1.G26
U1_H1: TP183.1, U1.H1
U1_H2: TP184.1, U1.H2
U1_H3: TP185.1, U1.H3
U1_H4: TP186.1, U1.H4
U1_H5: TP187.1, U1.H5
U1_H6: TP188.1, U1.H6
U1_H7: TP189.1, U1.H7
U1_H8: TP190.1, U1.H8
U1_H9: TP191.1, U1.H9
U1_H10: TP192.1, U1.H10
U1_H11: TP193.1, U1.H11
U1_H12: TP194.1, U1.H12
U1_H13: TP195.1, U1.H13
U1_H14: TP196.1, U1.H14
U1_H15: TP197.1, U1.H15
U1_H16: TP198.1, U1.H16
U1_H17: TP199.1, U1.H17
U1_H18: TP200.1, U1.H18
U1_H19: TP201.1, U1.H19
U1_H20: TP202.1, U1.H20
U1_H21: TP203.1, U1.H21
U1_H22: TP204.1, U1.H22
U1_H23: TP205.1, U1.H23
U1_H24: TP206.1, U1.H24
U1_H25: TP207.1, U1.H25
U1_H26: TP208.1, U1.H26
U1_J1: TP209.1, U1.J1
U1_J2: TP210.1, U1.J2
U1_J3: TP211.1, U1.J3
U1_J4: TP212.1, U1.J4
U1_J5: TP213.1, U1.J5
U1_J6: TP214.1, U1.J6
U1_J7: TP215.1, U1.J7
U1_J8: TP216.1, U1.J8
U1_J9: TP217.1, U1.J9
U1_J10: TP218.1, U1.J10
U1_J11: TP219.1, U1.J11
U1_J12: TP220.1, U1.J12
U1_J13: TP221.1, U1.J13
U1_J14: TP222.1, U1.J14
U1_J15: TP223.1, U1.J15
U1_J16: TP224.1, U1.J16
U1_J17: TP225.1, U1.J17
U1_J18: TP226.1, U1.J18
U1_J19: TP227.1, U1.J19
U1_J20: TP228.1, U1.J20
U1_J21: TP229.1, U1.J21
U1_J22: TP230.1, U1.J22
U1_J23: TP231.1, U1.J23
U1_J24: TP232.1, U1.J24
U1_J25: TP233.1, U1.J25
U1_J26: TP234.1, U1.J26
U1_K1: TP235.1, U1.K1
U1_K2: TP236.1, U1.K2
U1_K3: TP237.1, U1.K3
U1_K4: TP238.1, U1.K4
U1_K5: TP239.1, U1.K5
U1_K6: TP240.1, U1.K6
U1_K7: TP241.1, U1.K7
U1_K8: TP242.1, U1.K8
U1_K9: TP243.1, U1.K9
U1_K10: TP244.1, U1.K10
U1_K11: TP245.1, U1.K11
U1_K12: TP246.1, U1.K12
U1_K13: TP247.1, U1.K13
U1_K14: TP248.1, U1.K14
U1_K15: TP249.1, U1.K15
U1_K16: TP250.1, U1.K16
U1_K17: TP251.1, U1.K17
U1_K18: TP252.1, U1.K18
U1_K19: TP253.1, U1.K19
U1_K20: TP254.1, U1.K20
U1_K21: TP255.1, U1.K21
U1_K22: TP256.1, U1.K22
U1_K23: TP257.1, U1.K23
U1_K24: TP258.1, U1.K24
U1_K25: TP259.1, U1.K25
U1_K26: TP260.1, U1.K26
U1_L1: TP261.1, U1.L1
U1_L2: TP262.1, U1.L2
U1_L3: TP263.1, U1.L3
U1_L4: TP264.1, U1.L4
U1_L5: TP265.1, U1.L5
U1_L6: TP266.1, U1.L6
U1_L7: TP267.1, U1.L7
U1_L8: TP268.1, U1.L8
U1_L9: TP269.1, U1.L9
U1_L10: TP270.1, U1.L10
U1_L11: TP271.1, U1.L11
U1_L12: TP272.1, U1.L12
U1_L13: TP273.1, U1.L13
U1_L14: TP274.1, U1.L14
U1_L15: TP275.1, U1.L15
U1_L16: TP276.1, U1.L16
U1_L17: TP277.1, U1.L17
U1_L18: TP278.1, U1.L18
U1_L19: TP279.1, U1.L19
U1_L20: TP280.1, U1.L20
U1_L21: TP281.1, U1.L21
U1_L22: TP282.1, U1.L22
U1_L23: TP283.1, U1.L23
U1_L24: TP284.1, U1.L24
U1_L25: TP285.1, U1.L25
U1_L26: TP286.1, U1.L26
U1_M1: TP287.1, U1.M1
U1_M2: TP288.1, U1.M2
U1_M3: TP289.1, U1.M3
U1_M4: TP290.1, U1.M4
U1_M5: TP291.1, U1.M5
U1_M6: TP292.1, U1.M6
U1_M7: TP293.1, U1.M7
U1_M8: TP294.1, U1.M8
U1_M9: TP295.1, U1.M9
U1_M10: TP296.1, U1.M10
U1_M11: TP297.1, U1.M11
U1_M12: TP298.1, U1.M12
U1_M13: TP299.1, U1.M13
U1_M14: TP300.1, U1.M14
U1_M15: TP301.1, U1.M15
U1_M16: TP302.1, U1.M16
U1_M17: TP303.1, U1.M17
U1_M18: TP304.1, U1.M18
U1_M19: TP305.1, U1.M19
U1_M20: TP306.1, U1.M20
U1_M21: TP307.1, U1.M21
U1_M22: TP308.1, U1.M22
U1_M23: TP309.1, U1.M23
U1_M24: TP310.1, U1.M24
U1_M25: TP311.1, U1.M25
U1_M26: TP312.1, U1.M26
U1_N1: TP313.1, U1.N1
U1_N2: TP314.1, U1.N2
U1_N3: TP315.1, U1.N3
U1_N4: TP316.1, U1.N4
U1_N5: TP317.1, U1.N5
U1_N6: TP318.1, U1.N6
U1_N7: TP319.1, U1.N7
U1_N8: TP320.1, U1.N8
U1_N9: TP321.1, U1.N9
U1_N10: TP322.1, U1.N10
U1_N11: TP323.1, U1.N11
U1_N12: TP324.1, U1.N12
U1_N13: TP325.1, U1.N13
U1_N14: TP326.1, U1.N14
U1_N15: TP327.1, U1.N15
U1_N16: TP328.1, U1.N16
U1_N17: TP329.1, U1.N17
U1_N18: TP330.1, U1.N18
U1_N19: TP331.1, U1.N19
U1_N20: TP332.1, U1.N20
U1_N21: TP333.1, U1.N21
U1_N22: TP334.1, U1.N22
U1_N23: TP335.1, U1.N23
U1_N24: TP336.1, U1.N24
U1_N25: TP337.1, U1.N25
U1_N26: TP338.1, U1.N26
U1_P1: TP339.1, U1.P1
U1_P2: TP340.1, U1.P2
U1_P3: TP341.1, U1.P3
U1_P4: TP342.1, U1.P4
U1_P5: TP343.1, U1.P5
U1_P6: TP344.1, U1.P6
U1_P7: TP345.1, U1.P7
U1_P8: TP346.1, U1.P8
U1_P9: TP347.1, U1.P9
U1_P10: TP348.1, U1.P10
U1_P11: TP349.1, U1.P11
U1_P12: TP350.1, U1.P12
U1_P13: TP351.1, U1.P13
U1_P14: TP352.1, U1.P14
U1_P15: TP353.1, U1.P15
U1_P16: TP354.1, U1.P16
U1_P17: TP355.1, U1.P17
U1_P18: TP356.1, U1.P18
U1_P19: TP357.1, U1.P19
U1_P20: TP358.1, U1.P20
U1_P21: TP359.1, U1.P21
U1_P22: TP360.1, U1.P22
U1_P23: TP361.1, U1.P23
U1_P24: TP362.1, U1.P24
U1_P25: TP363.1, U1.P25
U1_P26: TP364.1, U1.P26
U1_R1: TP365.1, U1.R1
U1_R2: TP366.1, U1.R2
U1_R3: TP367.1, U1.R3
U1_R4: TP368.1, U1.R4
U1_R5: TP369.1, U1.R5
U1_R6: TP370.1, U1.R6
U1_R7: TP371.1, U1.R7
U1_R8: TP372.1, U1.R8
U1_R9: TP373.1, U1.R9
U1_R10: TP374.1, U1.R10
U1_R11: TP375.1, U1.R11
U1_R12: TP376.1, U1.R12
U1_R13: TP377.1, U1.R13
U1_R14: TP378.1, U1.R14
U1_R15: TP379.1, U1.R15
U1_R16: TP380.1, U1.R16
U1_R17: TP381.1, U1.R17
U1_R18: TP382.1, U1.R18
U1_R19: TP383.1, U1.R19
U1_R20: TP384.1, U1.R20
U1_R21: TP385.1, U1.R21
U1_R22: TP386.1, U1.R22
U1_R23: TP387.1, U1.R23
U1_R24: TP388.1, U1.R24
U1_R25: TP389.1, U1.R25
U1_R26: TP390.1, U1.R26
U1_T1: TP391.1, U1.T1
U1_T2: TP392.1, U1.T2
U1_T3: TP393.1, U1.T3
U1_T4: TP394.1, U1.T4
U1_T5: TP395.1, U1.T5
U1_T6: TP396.1, U1.T6
U1_T7: TP397.1, U1.T7
U1_T8: TP398.1, U1.T8
U1_T9: TP399.1, U1.T9
U1_T10: TP400.1, U1.T10
U1_T11: TP401.1, U1.T11
U1_T12: TP402.1, U1.T12
U1_T13: TP403.1, U1.T13
U1_T14: TP404.1, U1.T14
U1_T15: TP405.1, U1.T15
U1_T16: TP406.1, U1.T16
U1_T17: TP407.1, U1.T17
U1_T18: TP408.1, U1.T18
U1_T19: TP409.1, U1.T19
U1_T20: TP410.1, U1.T20
U1_T21: TP411.1, U1.T21
U1_T22: TP412.1, U1.T22
U1_T23: TP413.1, U1.T23
U1_T24: TP414.1, U1.T24
U1_T25: TP415.1, U1.T25
U1_T26: TP416.1, U1.T26
U1_U1: TP417.1, U1.U1
U1_U2: TP418.1, U1.U2
U1_U3: TP419.1, U1.U3
U1_U4: TP420.1, U1.U4
U1_U5: TP421.1, U1.U5
U1_U6: TP422.1, U1.U6
U1_U7: TP423.1, U1.U7
U1_U8: TP424.1, U1.U8
U1_U9: TP425.1, U1.U9
U1_U10: TP426.1, U1.U10
U1_U11: TP427.1, U1.U11
U1_U12: TP428.1, U1.U12
U1_U13: TP429.1, U1.U13
U1_U14: TP430.1, U1.U14
U1_U15: TP431.1, U1.U15
U1_U16: TP432.1, U1.U16
U1_U17: TP433.1, U1.U17
U1_U18: TP434.1, U1.U18
U1_U19: TP435.1, U1.U19
U1_U20: TP436.1, U1.U20
U1_U21: TP437.1, U1.U21
U1_U22: TP438.1, U1.U22
U1_U23: TP439.1, U1.U23
U1_U24: TP440.1, U1.U24
U1_U25: TP441.1, U1.U25
U1_U26: TP442.1, U1.U26
U1_V1: TP443.1, U1.V1
U1_V2: TP444.1, U1.V2
U1_V3: TP445.1, U1.V3
U1_V4: TP446.1, U1.V4
U1_V5: TP447.1, U1.V5
U1_V6: TP448.1, U1.V6
U1_V7: TP449.1, U1.V7
U1_V8: TP450.1, U1.V8
U1_V9: TP451.1, U1.V9
U1_V10: TP452.1, U1.V10
U1_V11: TP453.1, U1.V11
U1_V12: TP454.1, U1.V12
U1_V13: TP455.1, U1.V13
U1_V14: TP456.1, U1.V14
U1_V15: TP457.1, U1.V15
U1_V16: TP458.1, U1.V16
U1_V17: TP459.1, U1.V17
U1_V18: TP460.1, U1.V18
U1_V19: TP461.1, U1.V19
U1_V20: TP462.1, U1.V20
U1_V21: TP463.1, U1.V21
U1_V22: TP464.1, U1.V22
U1_V23: TP465.1, U1.V23
U1_V24: TP466.1, U1.V24
U1_V25: TP467.1, U1.V25
U1_V26: TP468.1, U1.V26
U1_W1: TP469.1, U1.W1
U1_W2: TP470.1, U1.W2
U1_W3: TP471.1, U1.W3
U1_W4: TP472.1, U1.W4
U1_W5: TP473.1, U1.W5
U1_W6: TP474.1, U1.W6
U1_W7: TP475.1, U1.W7
U1_W8: TP476.1, U1.W8
U1_W9: TP477.1, U1.W9
U1_W10: TP478.1, U1.W10
U1_W11: TP479.1, U1.W11
U1_W12: TP480.1, U1.W12
U1_W13: TP481.1, U1.W13
U1_W14: TP482.1, U1.W14
U1_W15: TP483.1, U1.W15
U1_W16: TP484.1, U1.W16
U1_W17: TP485.1, U1.W17
U1_W18: TP486.1, U1.W18
U1_W19: TP487.1, U1.W19
U1_W20: TP488.1, U1.W20
U1_W21: TP489.1, U1.W21
U1_W22: TP490.1, U1.W22
U1_W23: TP491.1, U1.W23
U1_W24: TP492.1, U1.W24
U1_W25: TP493.1, U1.W25
U1_W26: TP494.1, U1.W26
U1_Y1: TP495.1, U1.Y1
U1_Y2: TP496.1, U1.Y2
U1_Y3: TP497.1, U1.Y3
U1_Y4: TP498.1, U1.Y4
U1_Y5: TP499.1, U1.Y5
U1_Y6: TP500.1, U1.Y6
U1_Y7: TP501.1, U1.Y7
U1_Y8: TP502.1, U1.Y8
U1_Y9: TP503.1, U1.Y9
U1_Y10: TP504.1, U1.Y10
U1_Y11: TP505.1, U1.Y11
U1_Y12: TP506.1, U1.Y12
U1_Y13: TP507.1, U1.Y13
U1_Y14: TP508.1, U1.Y14
U1_Y15: TP509.1, U1.Y15
U1_Y16: TP510.1, U1.Y16
U1_Y17: TP511.1, U1.Y17
U1_Y18: TP512.1, U1.Y18
U1_Y19: TP513.1, U1.Y19
U1_Y20: TP514.1, U1.Y20
U1_Y21: TP515.1, U1.Y21
U1_Y22: TP516.1, U1.Y22
U1_Y23: TP517.1, U1.Y23
U1_Y24: TP518.1, U1.Y24
U1_Y25: TP519.1, U1.Y25
U1_Y26: TP520.1, U1.Y26

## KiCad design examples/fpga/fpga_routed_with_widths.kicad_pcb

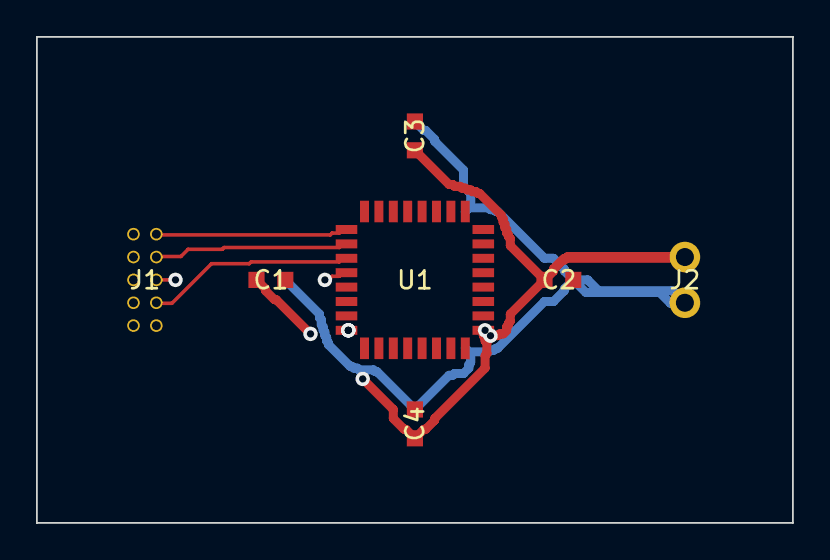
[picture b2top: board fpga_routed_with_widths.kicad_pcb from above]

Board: 4 copper layers, 42.0 x 27.0 mm, 7 parts (0 on the bottom side), 9 nets.

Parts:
C1, C2, C3, C4: 100nF; C_0603_1608Metric
J1: JTAG; PinHeader_2x05_P1.27mm_Vertical
J2: PWR; PinHeader_1x02_P2.54mm_Vertical
U1: FPGA; TQFP-32_7x7mm_P0.8mm

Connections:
GND: C1.2, C2.2, C3.2, C4.2, J2.2, U1.16, U1.32
GPIO1: U1.9, U1.25
GPIO2: U1.10, U1.26
SIG1: U1.5, U1.17
TCK: J1.4, U1.2
TDI: J1.8, U1.3
TDO: J1.6, U1.4
TMS: J1.2, U1.1
VCC: C1.1, C2.1, C3.1, C4.1, J2.1, U1.8, U1.24
